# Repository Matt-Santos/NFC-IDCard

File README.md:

The design of this multifunctional PCB business card focused on two key objectives: seamlessly transferring contact information and serving as a personal keycard for simple authentication tasks, such as home automation. The front side displays personal details in text, along with a QR code containing [vCard](https://en.wikipedia.org/wiki/VCard) information. The reverse side features useful engineering references and formulas. Behind the QR code, an internal NFC antenna with a surface-mounted [NT3H2211](https://www.nxp.com/products/rfid-nfc/nfc-hf/connected-nfc-tags/ntag-ic-plus-2k-nfc-forum-type-2-tag-with-ic-interface:NTAG_I2C) chip enables touch functionality for access control or as an additional method for transferring contact information.

Note: Be sure to update the phone number and QR code information before reprinting.

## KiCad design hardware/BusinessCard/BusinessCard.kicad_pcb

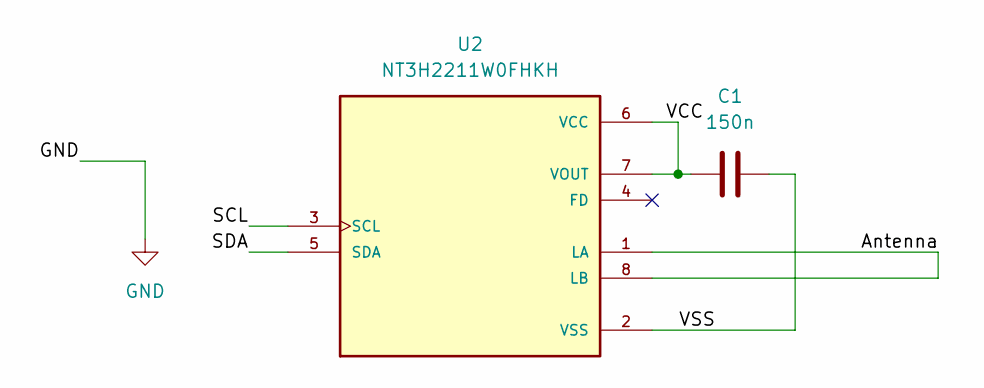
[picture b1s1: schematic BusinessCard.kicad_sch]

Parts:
C1: 150n; C_0201_0603Metric
U2: NT3H2211W0FHKH; IC_NT3H2211W0FHKH; PARTREV 3.4

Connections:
/Antenna: U2.1 (LA), U2.8 (LB)
/SCL: U2.3 (SCL)
/SDA: U2.5 (SDA)
/VCC: C1.2, U2.6 (VCC), U2.7 (VOUT)
/VSS: C1.1, U2.2 (VSS)

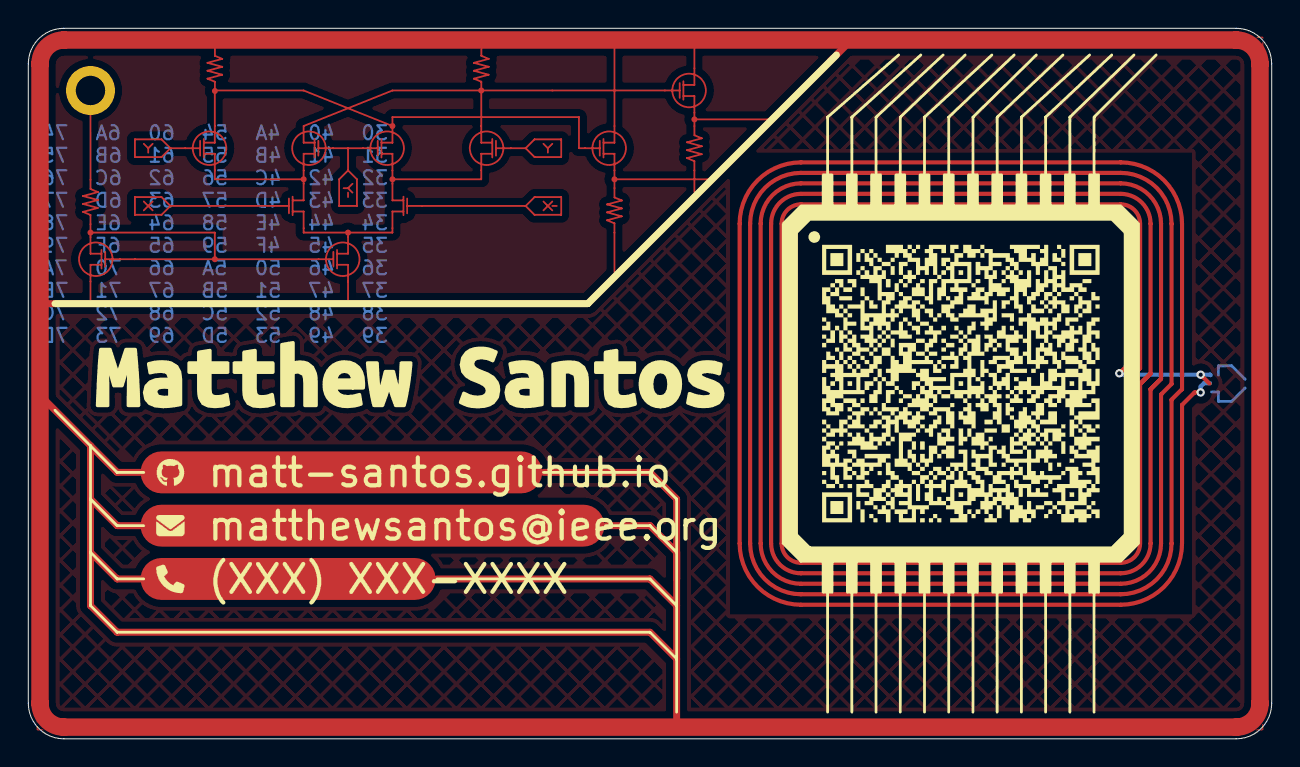
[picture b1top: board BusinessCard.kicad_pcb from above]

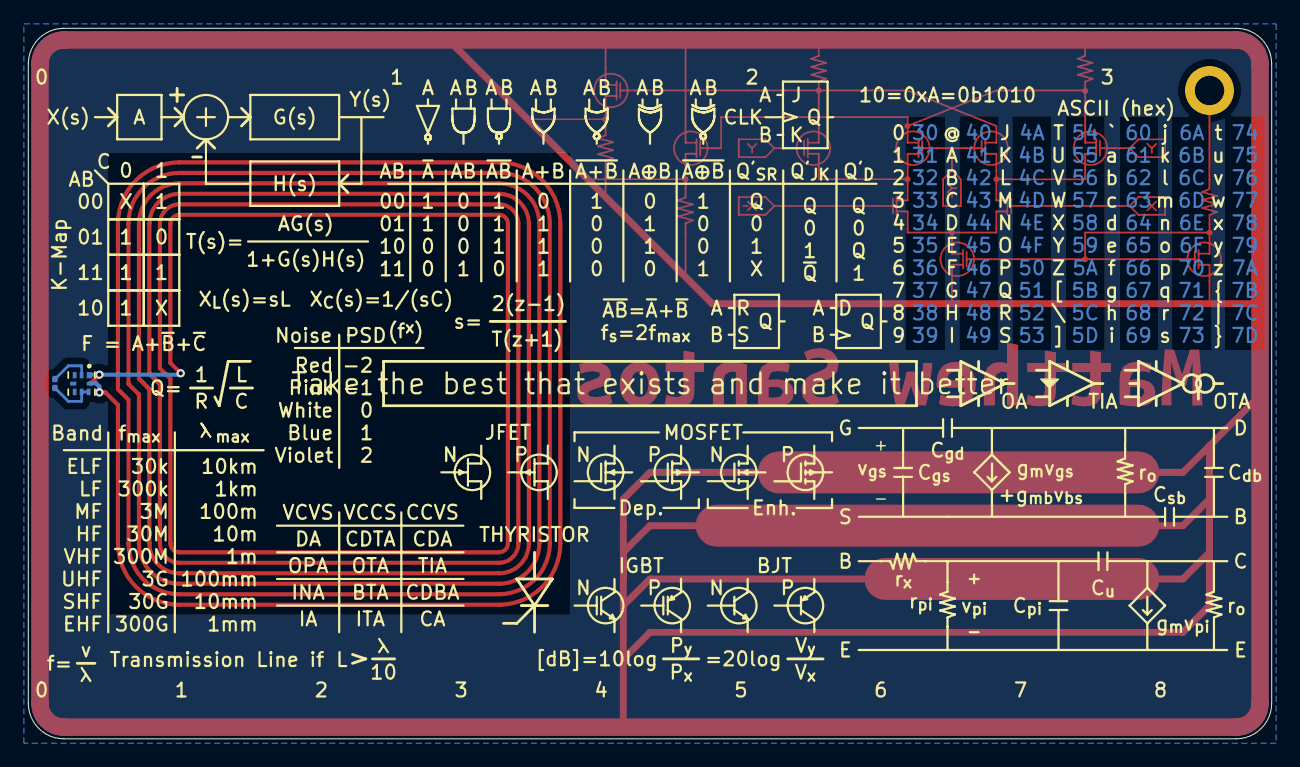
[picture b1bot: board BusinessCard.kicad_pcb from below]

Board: 2 copper layers, 88.9 x 50.8 mm, 4 parts (2 on the bottom side), 3 nets.

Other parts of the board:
kibuzzard-6765DA2E: G***; kibuzzard-6765DA2E
kibuzzard-6765DA4E: G***; kibuzzard-6765DA4E

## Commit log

2024-12-21 feat: add hardware files
2025-01-03 feat: add gallery and project images
2025-01-10 feat: add readme documentation
2025-01-10 fix: invalid pcb comment
